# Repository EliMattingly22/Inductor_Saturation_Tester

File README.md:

# Inductor_Saturation_Tester
A circuit to check the saturation level of different inductor cores

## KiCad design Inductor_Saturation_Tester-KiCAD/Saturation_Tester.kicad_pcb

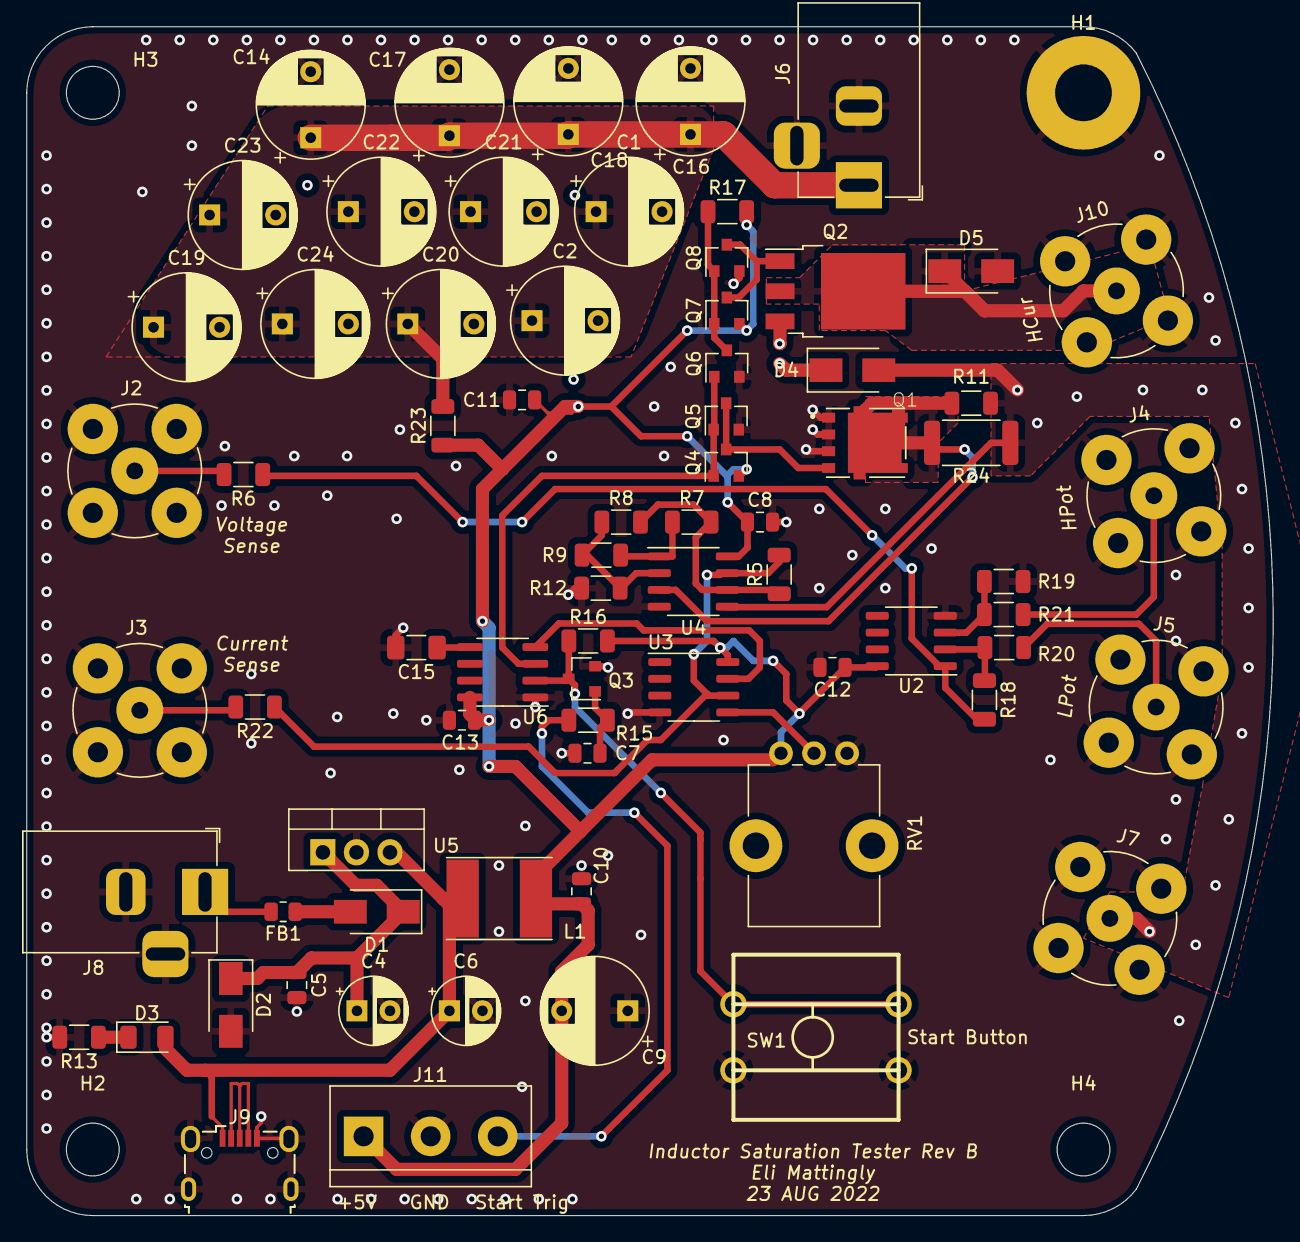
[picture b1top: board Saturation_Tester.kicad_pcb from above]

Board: 2 copper layers, 94.4 x 90.0 mm, 78 parts (1 on the bottom side), 33 nets.

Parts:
C1, C2, C14, C16, C17, C18, C19, C20, C21, C22, C23, C24: 100u; CP_Radial_D8.0mm_P5.00mm
C3, C8, C10, C12, C13: 100n; C_0805_2012Metric
C4, C6: CP; CP_Radial_D5.0mm_P2.50mm
C5, C11: C; C_0805_2012Metric
C7: 1u; C_0805_2012Metric
C9: CP; CP_Radial_D8.0mm_P5.00mm
C15: 10n; C_1206_3216Metric_Pad1.33x1.80mm_HandSolder
D1: D; D_SMA
D2: D_TVS; D_SMA
D3: LED; LED_1206_3216Metric
D4, D5: D_Schottky; D_SMA
FB1: Ferrite_Bead; R_0805_2012Metric
H1: MountingHole_Pad; MountingHole_4.3mm_M4_Pad
H2, H3, H4: MountingHole; MountingHole_4mm
J2, J3, J4, J5, J7, J10: Conn_Coaxial; BNC_TEConnectivity_1478204_Vertical
J6, J8: Barrel_Jack_Switch; BarrelJack_Horizontal
J9: USB_B_Micro; USB_Micro-B_Wuerth_629105150521
J11: Screw_Terminal_01x03; TerminalBlock_bornier-3_P5.08mm
L1: 10u; L_Taiyo-Yuden_NR-60xx_HandSoldering
Q1: NTMFS4C029N; DIO_NTS1045EMFST1G
Q2: DMP4015SK3; TO-252-3_TabPin4
Q3, Q5, Q6, Q8: DMN67D7L; SOT-23
Q4, Q7: BSS84; SOT-23
R5, R7, R9, R12, R13, R15, R16, R17, R18, R19, R20, R21: 1k; R_1206_3216Metric
R6, R22: 47; R_1206_3216Metric
R8: 249; R_1206_3216Metric
R11: DNP; R_1206_3216Metric
R23: 22; R_1206_3216Metric
R24: 10m; R_2512_6332Metric
RV1: R_POT; Potentiometer_Bourns_PTV09A-1_Single_Vertical
SW1: SW_MEC_5E; BigButton_TL1100F160Q
U2, U3, U4: LM358; SO-8_3.9x4.9mm_P1.27mm
U5: L7805; TO-220-3_Vertical
U6: NE555D; SOIC-8_3.9x4.9mm_P1.27mm

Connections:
+5V: C6.1, D3.2 (A), J9.1 (VBUS), L1.2, U5.3 (OUT)
+5VP: C3.1, C8.1, C9.2, C10.1, C11.1, C12.1, C13.1, J11.1, L1.1, Q4.2 (S), Q7.2 (S), R16.2, R17.2, R23.1, RV1.1, U2.8 (V+), U3.8 (V+), U4.8 (V+), U6.8 (VCC)
AltPower: C1.1, C2.1, C14.1, C16.1, C17.1, C18.1, C19.1, C20.1, C21.1, C22.1, C23.1, C24.1, D4.1 (K), J6.1, Q2.3 (S), R23.2
GND: C1.2, C2.2, C3.2, C4.2, C5.2, C6.2, C7.2, C8.2, C9.1, C10.2, C11.2, C12.2, C13.2, C14.2, C15.2, C16.2, C17.2, C18.2, C19.2, C20.2, C21.2, C22.2, C23.2, C24.2, D2.2 (A2), D5.2 (A), H1.1, J2.2 (Ext), J3.2 (Ext), J4.2 (Ext), J5.2 (Ext), J6.2, J6.3, J7.2 (Ext), J8.2, J8.3, J9.5 (GND), J9.6 (Shield), J10.2 (Ext), J11.2, Q1.1 (S), Q1.2 (S), Q1.3 (S), Q3.2 (S), Q5.2 (S), Q6.2 (S), Q8.2 (S), R12.1, R13.2, R19.2, RV1.3, SW1.3 (K), SW1.4 (A), U2.4 (V-), U3.4 (V-), U4.4 (V-), U5.2 (GND), U6.1 (GND)
IOut: D5.1 (K), J10.1 (In), Q2.2 (D), Q2.4 (D)
I_Lim_Comp: U3.7, U6.4 (R)
InputLogic: J11.3, R15.2
NMOS_Gate: Q1.4 (G), Q4.3 (D), Q5.3 (D)
unnamed: C4.1, C5.1, D1.1 (K), D2.1 (A1), U5.1 (IN)
unnamed: C7.1, Q3.1 (G), R15.1
unnamed: C15.1, U6.5 (CV)
unnamed: D1.2 (A), FB1.1
unnamed: D3.1 (K), R13.1
unnamed: FB1.2, J8.1
unnamed: J2.1 (In), R6.2
unnamed: J3.1 (In), R22.2
unnamed: J4.1 (In), R21.1
unnamed: J5.1 (In), R20.1
unnamed: J9.2 (D-), J9.3 (D+), J9.4 (ID)
unnamed: R5.1, R7.2, R8.2, U4.6 (-)
unnamed: R7.1, R9.2, U4.1
unnamed: R8.1, R9.1, R12.2, U4.2 (-)
unnamed: Q3.3 (D), R16.1, SW1.1, SW1.2, U6.2 (TR)
unnamed: Q6.3 (D), Q7.1 (G), Q8.1 (G), R17.1
unnamed: R18.1, R20.2, U2.2 (-)
unnamed: R6.1, R18.2, U2.1
unnamed: R19.1, R21.2, U2.3 (+)
unnamed: R5.2, R22.1, U3.6 (-), U4.7
unnamed: RV1.2, U3.5 (+)
PMOS_Gate: Q2.1 (G), Q7.3 (D), Q8.3 (D)
RShunt+: D4.2 (A), J7.1 (In), R11.2, R24.1, U4.5 (+)
RShunt-: Q1.5 (D), R11.1, R24.2, U4.3 (+)
TurnOn: Q4.1 (G), Q5.1 (G), Q6.1 (G), U6.3 (Q)

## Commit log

2021-12-25 Initialize
2022-08-23 Rev B Update
2022-08-23 update Rev B
